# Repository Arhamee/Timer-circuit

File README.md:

# Timer-circuit
A timer circuit 
This project demonstrates a 555 timer-based auto-cutoff circuit that automatically turns off AC-powered devices (like lights or fans) after a preset time delay. The circuit uses the NE555 IC in monostable mode, where a trigger signal activates the timer, keeping the output high for a fixed duration (adjustable via RC components) before cutting off power. Key components include the 555 timer, a relay module (for AC switching), a potentiometer (for time adjustment), and supporting resistors/capacitors. The delay time can be calculated using T ≈ 1.1 × R × C, allowing customization from seconds to hours. The relay isolates the low-voltage DC timer circuit from the high-voltage AC load, ensuring safety. Ideal for energy-saving applications, workshop tools

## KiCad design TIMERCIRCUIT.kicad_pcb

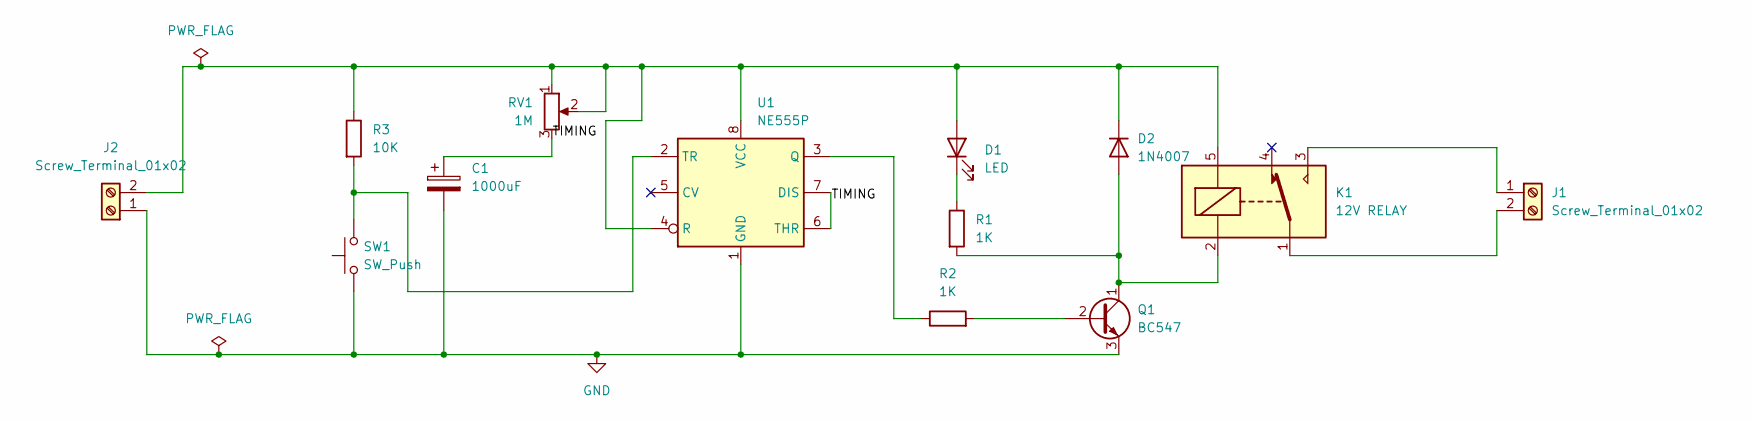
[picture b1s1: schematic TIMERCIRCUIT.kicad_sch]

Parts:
C1: 1000uF; CP_Radial_D10.0mm_P3.50mm
D1: LED; LED_D3.0mm_Horizontal_O1.27mm_Z2.0mm_IRGrey
D2: 1N4007; D_DO-41_SOD81_P10.16mm_Horizontal
J1, J2: Screw_Terminal_01x02; TerminalBlock_MaiXu_MX126-5.0-02P_1x02_P5.00mm
K1: 12V RELAY; Relay_SPDT_SANYOU_SRD_Series_Form_C
Q1: BC547; TO-92_Inline
R1, R2: 1K; R_Axial_DIN0207_L6.3mm_D2.5mm_P10.16mm_Horizontal
R3: 10K; R_Axial_DIN0207_L6.3mm_D2.5mm_P10.16mm_Horizontal
RV1: 1M; Potentiometer_Bourns_3296W_Vertical
SW1: SW_Push; SW_PUSH-12mm
U1: NE555P; DIP-8_W7.62mm

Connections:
/TIMING: C1.1, RV1.3, U1.6 (THR), U1.7 (DIS)
GND: C1.2, J2.1, Q1.3 (E), SW1.1, U1.1 (GND)
unnamed: D1.2 (A), D2.1 (K), J2.2, K1.5, R3.1, RV1.1, RV1.2, U1.4 (R), U1.8 (VCC)
unnamed: D1.1 (K), R1.1
unnamed: D2.2 (A), K1.2, Q1.1 (C), R1.2
unnamed: J1.1, K1.3
unnamed: J1.2, K1.1
unnamed: Q1.2 (B), R2.2
unnamed: R2.1, U1.3 (Q)
unnamed: R3.2, SW1.2, U1.2 (TR)

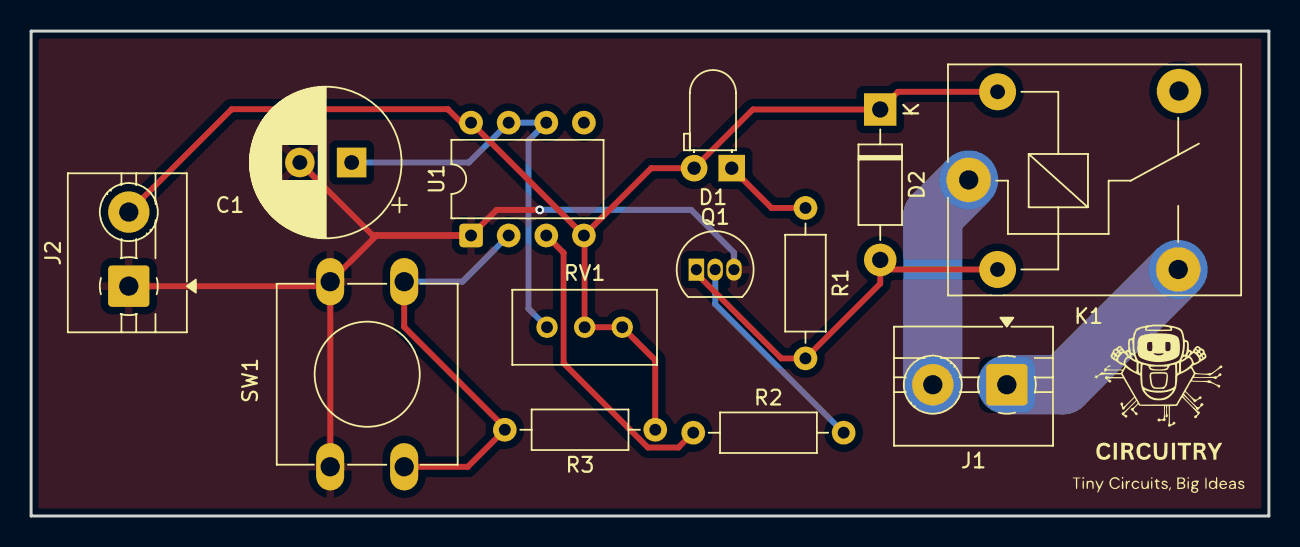
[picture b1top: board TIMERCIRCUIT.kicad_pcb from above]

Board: 2 copper layers, 83.6 x 32.8 mm, 13 parts (0 on the bottom side), 10 nets.
